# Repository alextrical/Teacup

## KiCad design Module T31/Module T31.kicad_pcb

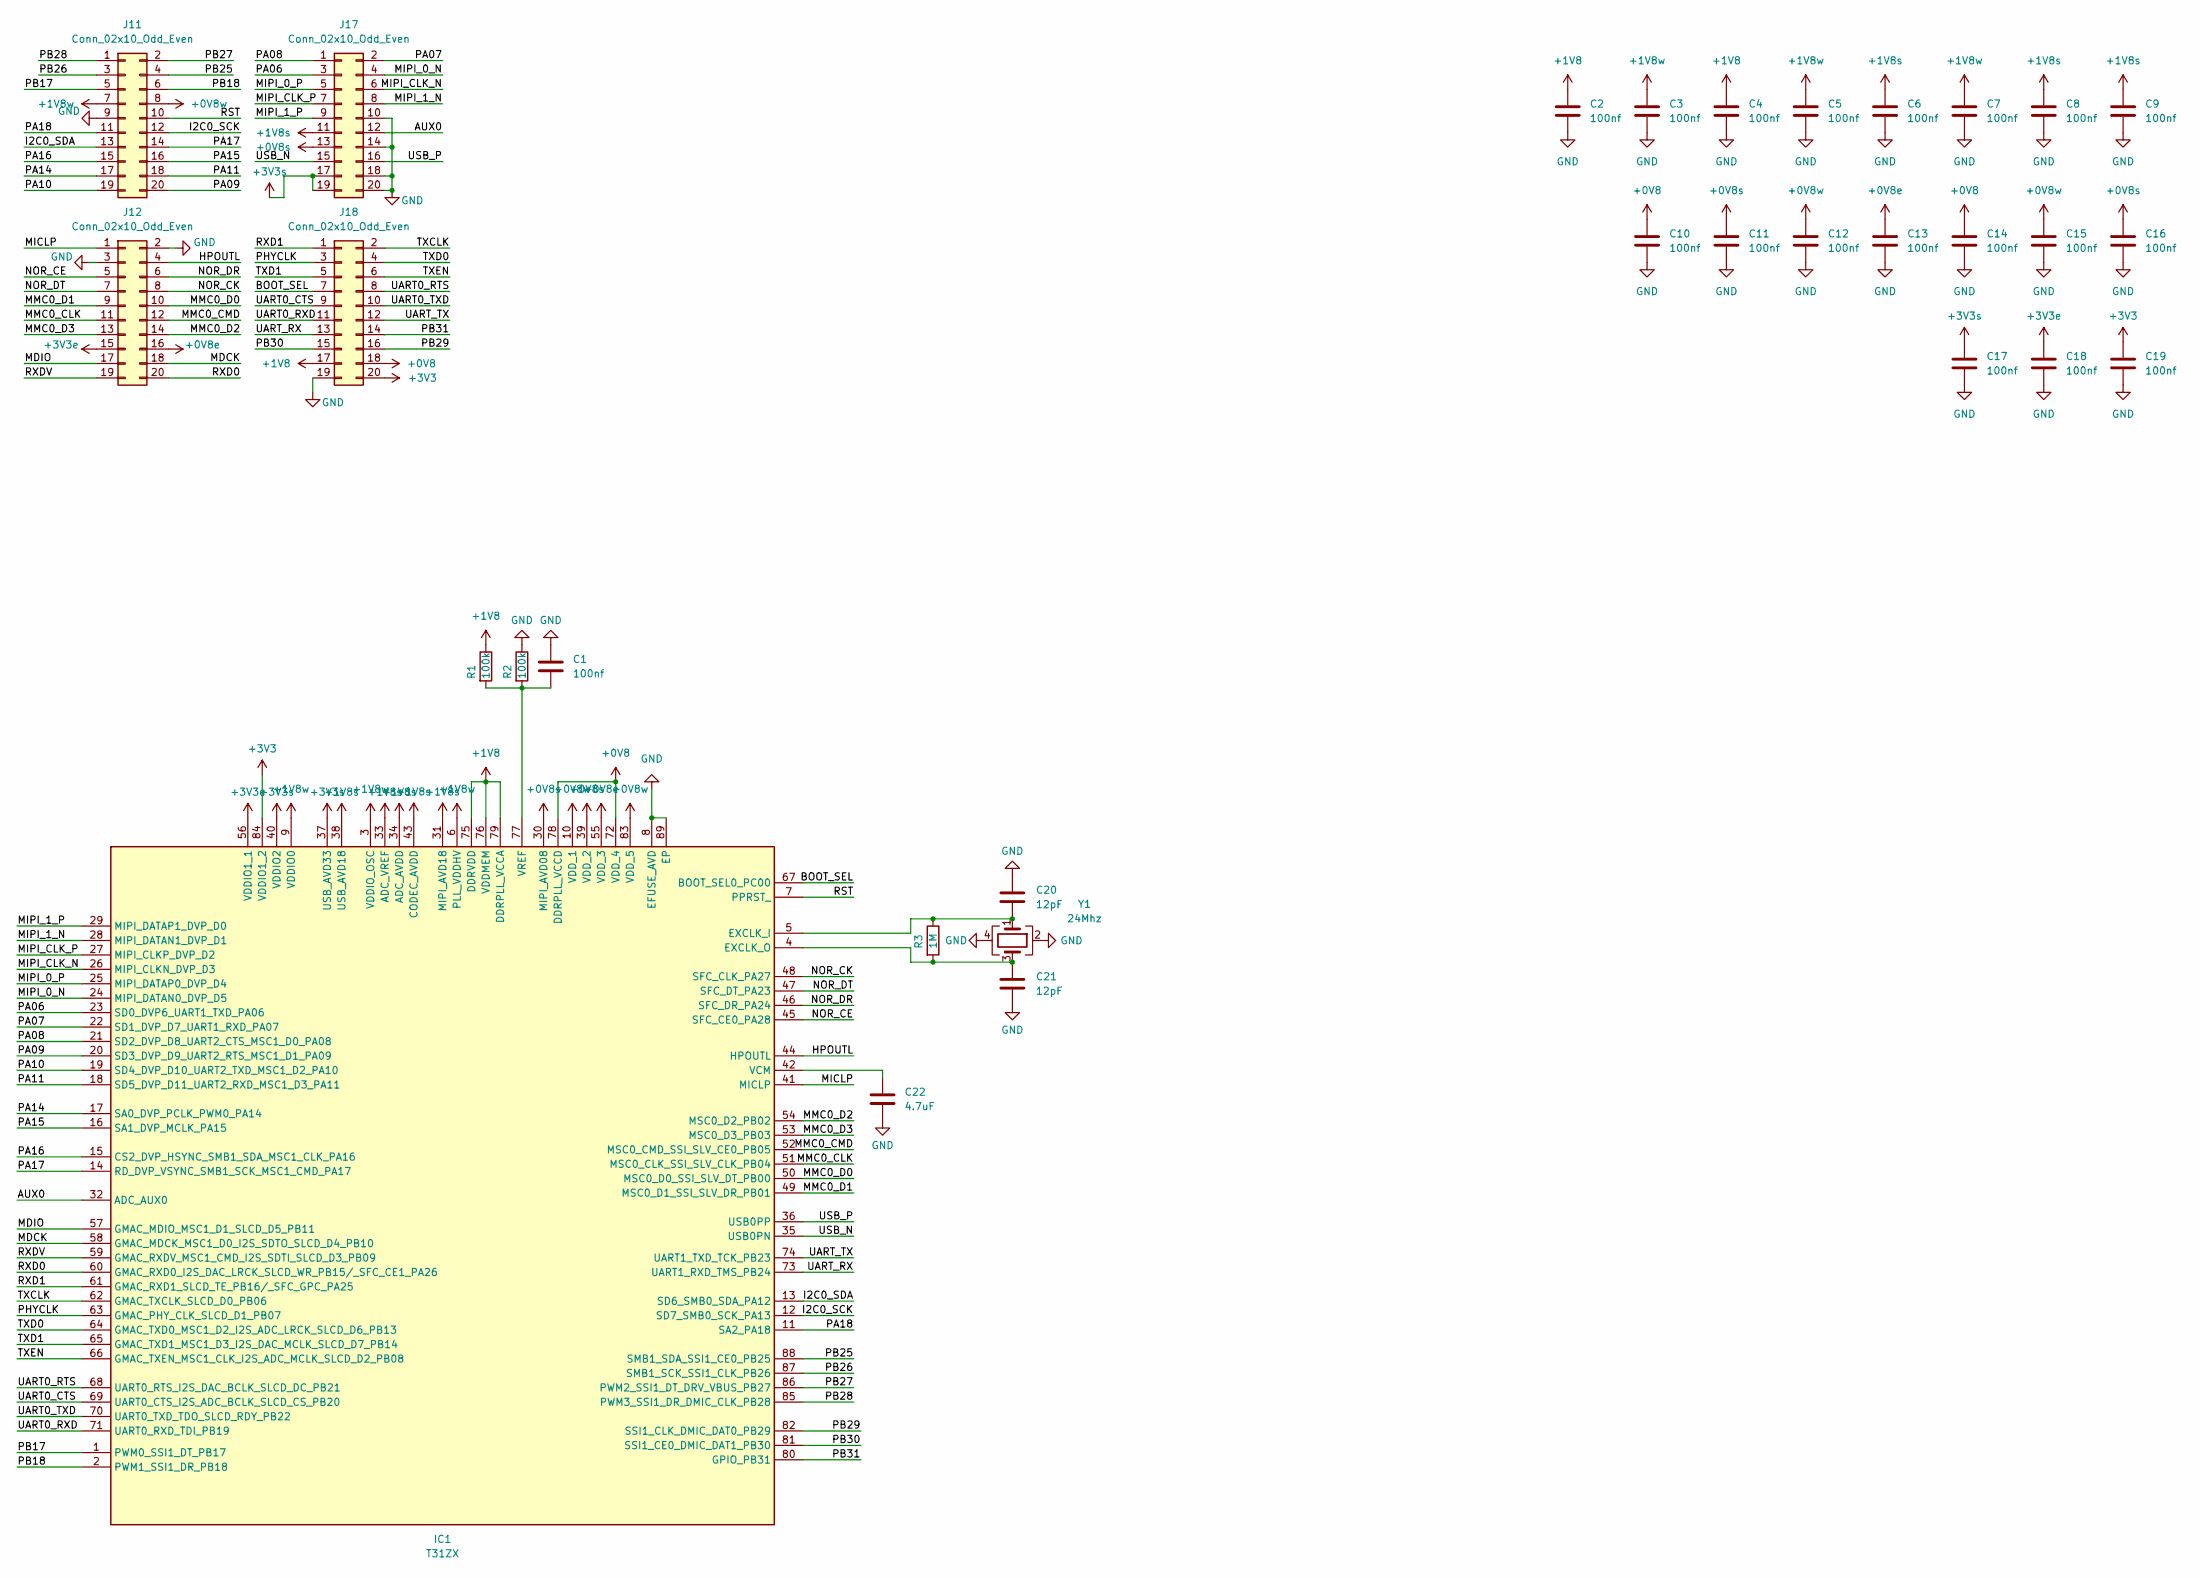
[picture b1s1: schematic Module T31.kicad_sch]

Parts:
C1, C2, C3, C4, C5, C6, C7, C8, C9, C10, C11, C12, C13, C14, C15, C16, C17, C18, C19: 100nf; C_0402_1005Metric; LCSC C1525
C20, C21: 12pF; C_0402_1005Metric; LCSC C1547
C22: 4.7uF; C_0402_1005Metric; LCSC C23733
IC1: T31ZX; QFN35P900X900X90-89N-D; Mouser Part Number 870-T31ZX
J11, J12, J17, J18: Conn_02x10_Odd_Even; PinHeader_2x10_P2.54mm_Vertical
R1, R2: 100k; R_0402_1005Metric; LCSC C25741
R3: 1M; R_0402_1005Metric; LCSC C26083
Y1: 24Mhz; Crystal_SMD_2016-4Pin_2.0x1.6mm; LCSC C557195

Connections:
+0V8: C10.1, C14.1, IC1.72 (VDD_4), IC1.78 (DDRPLL_VCCD), J18.18
+0V8e: C13.1, IC1.55 (VDD_3), J12.16
+0V8s: C11.1, C16.1, IC1.30 (MIPI_AVD08), IC1.39 (VDD_2), J17.13
+0V8w: C12.1, C15.1, IC1.10 (VDD_1), IC1.83 (VDD_5), J11.8
+1V8: C2.1, C4.1, IC1.75 (DDRVDD), IC1.76 (VDDMEM), IC1.79 (DDRPLL_VCCA), J18.17, R1.1
+1V8s: C6.1, C8.1, C9.1, IC1.31 (MIPI_AVD18), IC1.33 (ADC_VREF), IC1.34 (ADC_AVDD), IC1.38 (USB_AVD18), IC1.43 (CODEC_AVDD), J17.11
+1V8w: C3.1, C5.1, C7.1, IC1.3 (VDDIO_OSC), IC1.6 (PLL_VDDHV), IC1.9 (VDDIO0), J11.7
+3V3: C19.1, IC1.84 (VDDIO1_2), J18.20
+3V3e: C18.1, IC1.56 (VDDIO1_1), J12.15
+3V3s: C17.1, IC1.37 (USB_AVD33), IC1.40 (VDDIO2), J17.17, J17.19
/AUX0: IC1.32 (ADC_AUX0), J17.12
/BOOT_SEL: IC1.67 (BOOT_SEL0_PC00), J18.7
/HPOUTL: IC1.44 (HPOUTL), J12.4
/I2C0_SCK: IC1.12 (SD7_SMB0_SCK_PA13), J11.12
/I2C0_SDA: IC1.13 (SD6_SMB0_SDA_PA12), J11.13
/MDCK: IC1.58 (GMAC_MDCK_MSC1_D0_I2S_SDTO_SLCD_D4_PB10), J12.18
/MDIO: IC1.57 (GMAC_MDIO_MSC1_D1_SLCD_D5_PB11), J12.17
/MICLP: IC1.41 (MICLP), J12.1
/MIPI_0_N: IC1.24 (MIPI_DATAN0_DVP_D5), J17.4
/MIPI_0_P: IC1.25 (MIPI_DATAP0_DVP_D4), J17.5
/MIPI_1_N: IC1.28 (MIPI_DATAN1_DVP_D1), J17.8
/MIPI_1_P: IC1.29 (MIPI_DATAP1_DVP_D0), J17.9
/MIPI_CLK_N: IC1.26 (MIPI_CLKN_DVP_D3), J17.6
/MIPI_CLK_P: IC1.27 (MIPI_CLKP_DVP_D2), J17.7
/MMC0_CLK: IC1.51 (MSC0_CLK_SSI_SLV_CLK_PB04), J12.11
/MMC0_CMD: IC1.52 (MSC0_CMD_SSI_SLV_CE0_PB05), J12.12
/MMC0_D0: IC1.50 (MSC0_D0_SSI_SLV_DT_PB00), J12.10
/MMC0_D1: IC1.49 (MSC0_D1_SSI_SLV_DR_PB01), J12.9
/MMC0_D2: IC1.54 (MSC0_D2_PB02), J12.14
/MMC0_D3: IC1.53 (MSC0_D3_PB03), J12.13
/NOR_CE: IC1.45 (SFC_CE0_PA28), J12.5
/NOR_CK: IC1.48 (SFC_CLK_PA27), J12.8
/NOR_DR: IC1.46 (SFC_DR_PA24), J12.6
/NOR_DT: IC1.47 (SFC_DT_PA23), J12.7
/PA06: IC1.23 (SD0_DVP6_UART1_TXD_PA06), J17.3
/PA07: IC1.22 (SD1_DVP_D7_UART1_RXD_PA07), J17.2
/PA08: IC1.21 (SD2_DVP_D8_UART2_CTS_MSC1_D0_PA08), J17.1
/PA09: IC1.20 (SD3_DVP_D9_UART2_RTS_MSC1_D1_PA09), J11.20
/PA10: IC1.19 (SD4_DVP_D10_UART2_TXD_MSC1_D2_PA10), J11.19
/PA11: IC1.18 (SD5_DVP_D11_UART2_RXD_MSC1_D3_PA11), J11.18
/PA14: IC1.17 (SA0_DVP_PCLK_PWM0_PA14), J11.17
/PA15: IC1.16 (SA1_DVP_MCLK_PA15), J11.16
/PA16: IC1.15 (CS2_DVP_HSYNC_SMB1_SDA_MSC1_CLK_PA16), J11.15
/PA17: IC1.14 (RD_DVP_VSYNC_SMB1_SCK_MSC1_CMD_PA17), J11.14
/PA18: IC1.11 (SA2_PA18), J11.11
/PB17: IC1.1 (PWM0_SSI1_DT_PB17), J11.5
/PB18: IC1.2 (PWM1_SSI1_DR_PB18), J11.6
/PB25: IC1.88 (SMB1_SDA_SSI1_CE0_PB25), J11.4
/PB26: IC1.87 (SMB1_SCK_SSI1_CLK_PB26), J11.3
/PB27: IC1.86 (PWM2_SSI1_DT_DRV_VBUS_PB27), J11.2
/PB28: IC1.85 (PWM3_SSI1_DR_DMIC_CLK_PB28), J11.1
/PB29: IC1.82 (SSI1_CLK_DMIC_DAT0_PB29), J18.16
/PB30: IC1.81 (SSI1_CE0_DMIC_DAT1_PB30), J18.15
/PB31: IC1.80 (GPIO_PB31), J18.14
/PHYCLK: IC1.63 (GMAC_PHY_CLK_SLCD_D1_PB07), J18.3
/RST: IC1.7 (PPRST_), J11.10
/RXD0: IC1.60 (GMAC_RXD0_I2S_DAC_LRCK_SLCD_WR_PB15/_SF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), J12.20
/RXD1: IC1.61 (GMAC_RXD1_SLCD_TE_PB16/_SFC_GPC_PA25), J18.1
/RXDV: IC1.59 (GMAC_RXDV_MSC1_CMD_I2S_SDTI_SLCD_D3_PB09), J12.19
/TXCLK: IC1.62 (GMAC_TXCLK_SLCD_D0_PB06), J18.2
/TXD0: IC1.64 (GMAC_TXD0_MSC1_D2_I2S_ADC_LRCK_SLCD_D6_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), J18.4
/TXD1: IC1.65 (GMAC_TXD1_MSC1_D3_I2S_DAC_MCLK_SLCD_D7_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), J18.5
/TXEN: IC1.66 (GMAC_TXEN_MSC1_CLK_I2S_ADC_MCLK_SLCD_D2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), J18.6
/UART0_CTS: IC1.69 (UART0_CTS_I2S_ADC_BCLK_SLCD_CS_PB20), J18.9
/UART0_RTS: IC1.68 (UART0_RTS_I2S_DAC_BCLK_SLCD_DC_PB21), J18.8
/UART0_RXD: IC1.71 (UART0_RXD_TDI_PB19), J18.11
/UART0_TXD: IC1.70 (UART0_TXD_TDO_SLCD_RDY_PB22), J18.10
/UART_RX: IC1.73 (UART1_RXD_TMS_PB24), J18.13
/UART_TX: IC1.74 (UART1_TXD_TCK_PB23), J18.12
/USB_N: IC1.35 (USB0PN), J17.15
/USB_P: IC1.36 (USB0PP), J17.16
GND: C1.1, C2.2, C3.2, C4.2, C5.2, C6.2, C7.2, C8.2, C9.2, C10.2, C11.2, C12.2, C13.2, C14.2, C15.2, C16.2, C17.2, C18.2, C19.2, C20.1, C21.2, C22.2, IC1.8 (EFUSE_AVD), IC1.89 (EP), J11.9, J12.2, J12.3, J17.10, J17.14, J17.18, J17.20, J18.19, R2.1, Y1.2, Y1.4
unnamed: C20.2, IC1.5 (EXCLK_I), R3.1, Y1.1
unnamed: C21.1, IC1.4 (EXCLK_O), R3.2, Y1.3
unnamed: C22.1, IC1.42 (VCM)
unnamed: C1.2, IC1.77 (VREF), R1.2, R2.2

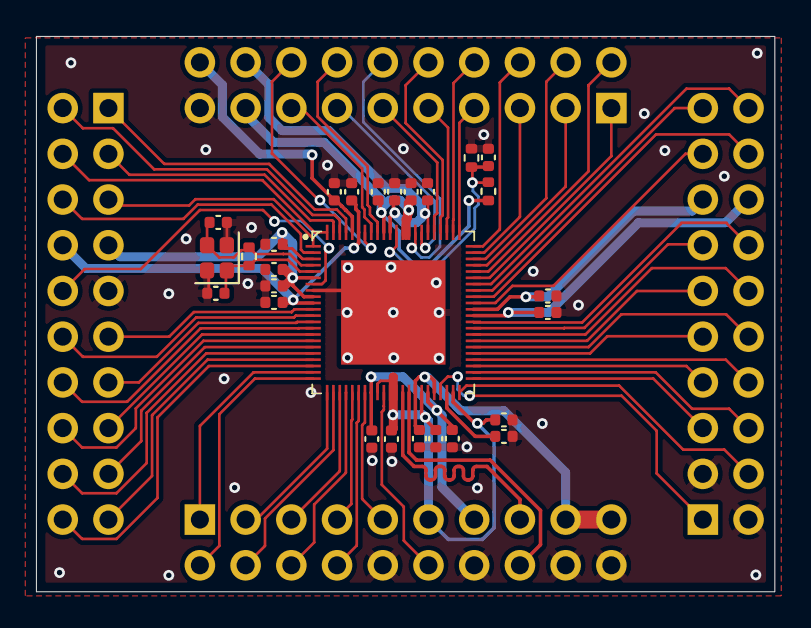
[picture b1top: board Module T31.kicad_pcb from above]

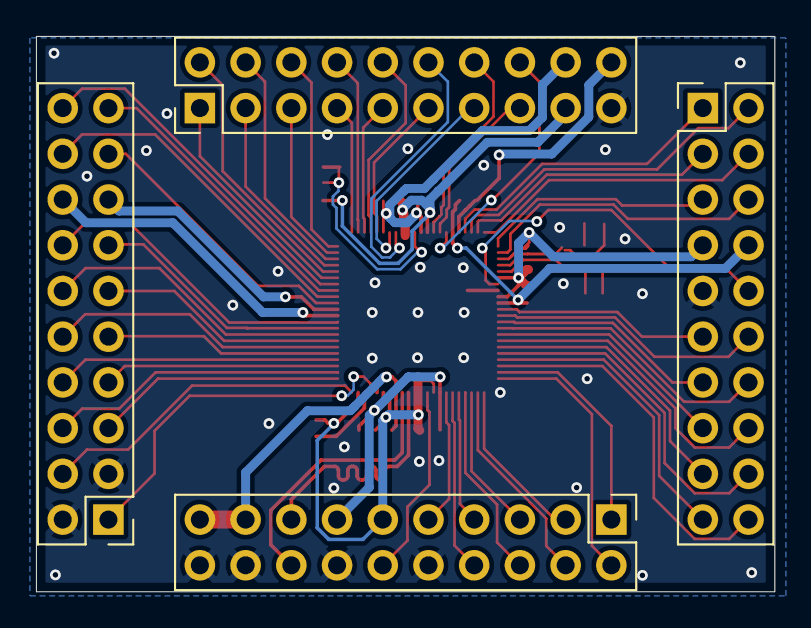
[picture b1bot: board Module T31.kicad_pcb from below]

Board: 4 copper layers, 41.0 x 30.8 mm, 31 parts (4 on the bottom side), 76 nets.

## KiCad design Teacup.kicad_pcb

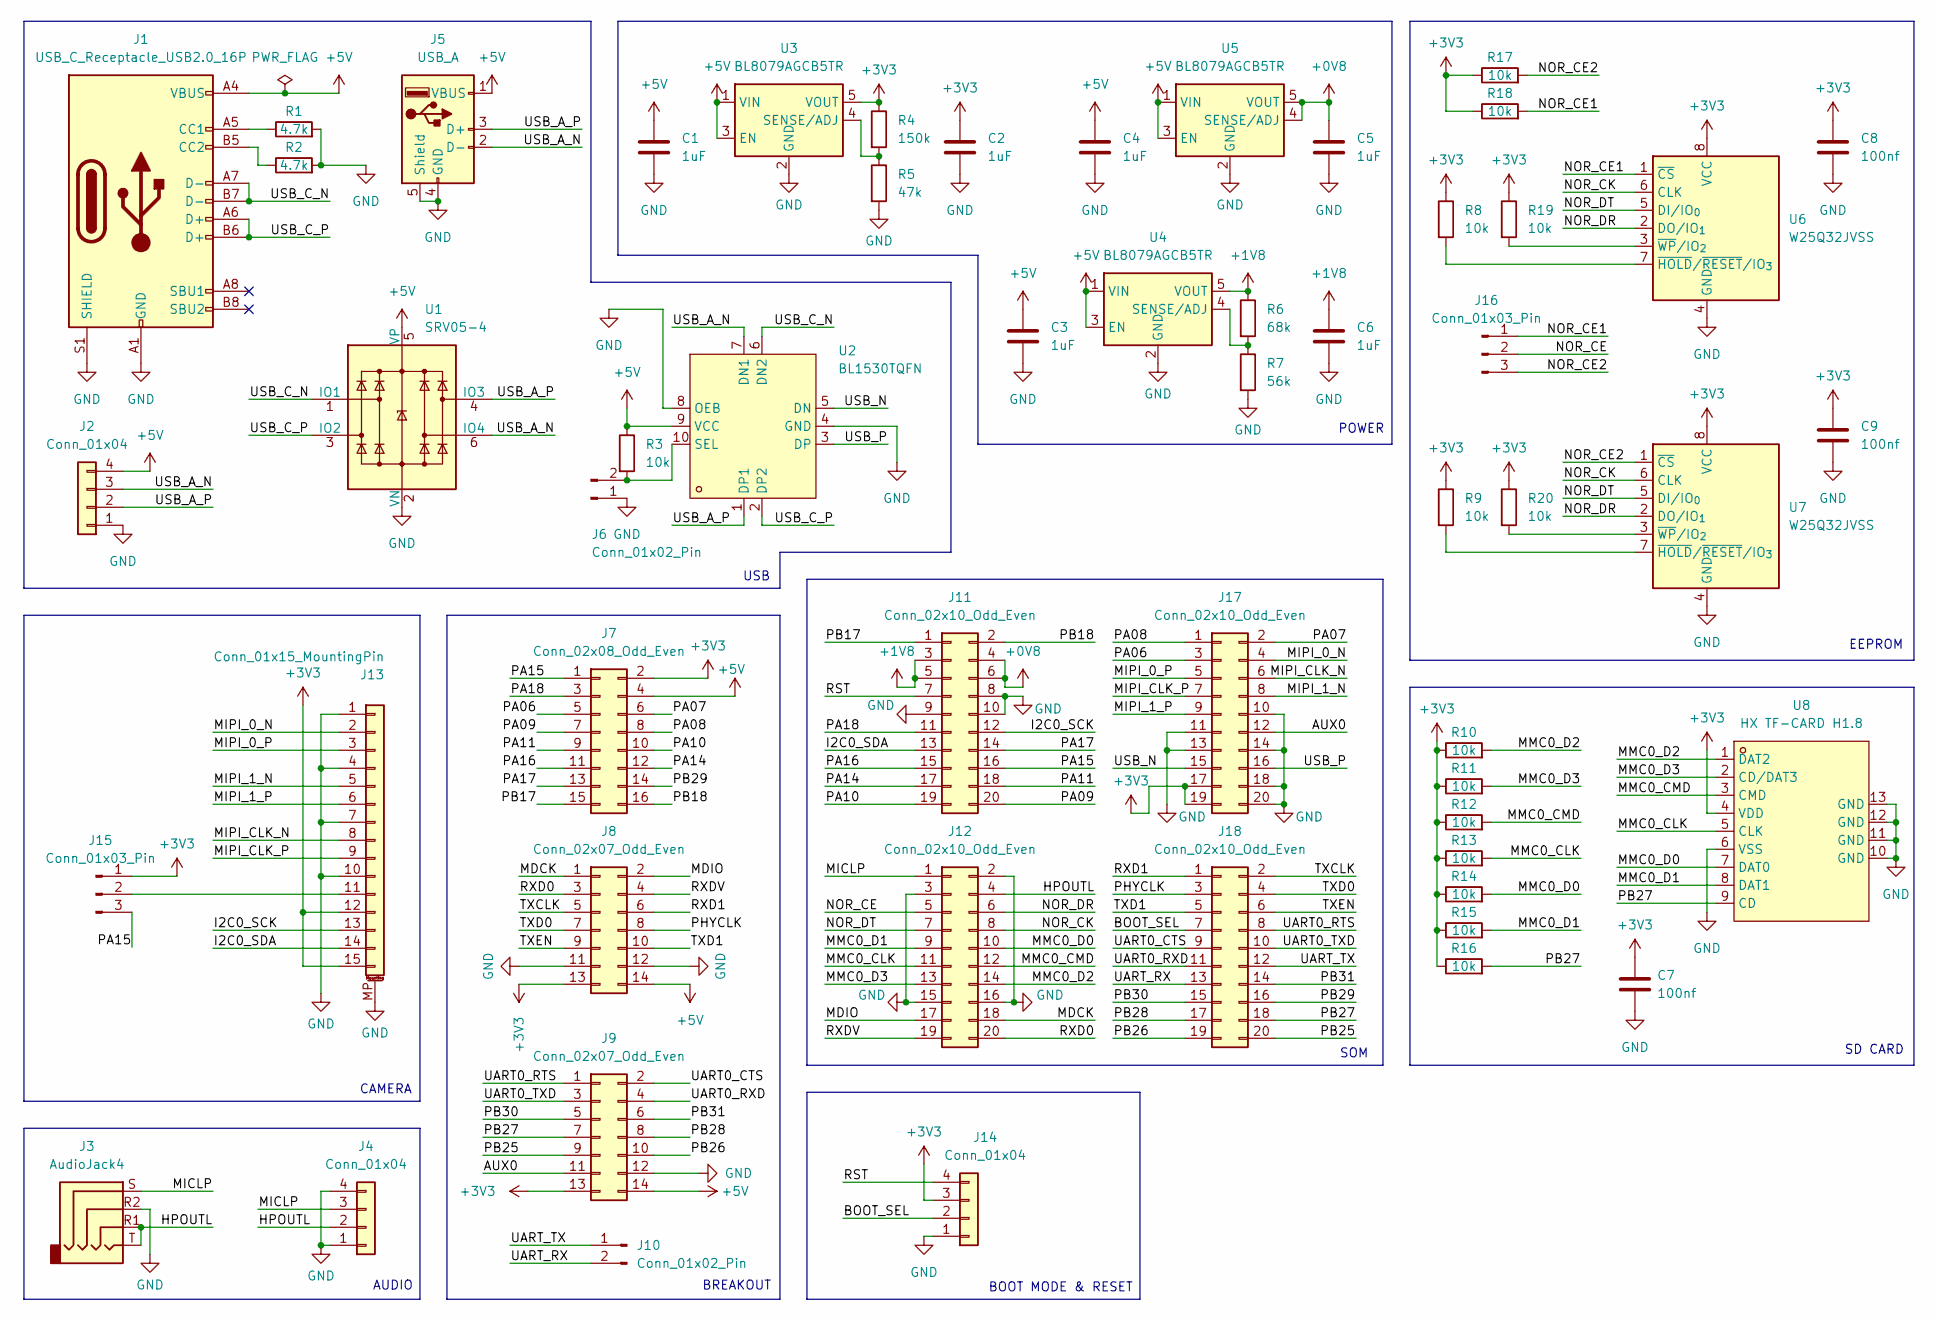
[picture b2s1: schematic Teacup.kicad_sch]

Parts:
C1, C2, C3, C4, C5, C6: 1uF; C_0402_1005Metric; LCSC C52923
C7, C8, C9: 100nf; C_0603_1608Metric; LCSC C14663
J1: USB_C_Receptacle_USB2.0_16P; USB_C_Receptacle_G-Switch_GT-USB-7010ASV; LCSC C36936538
J2, J4, J14: Conn_01x04; PinHeader_1x04_P2.54mm_Vertical
J3: AudioJack4; Jack_3.5mm_PJ320D_Horizontal
J5: USB_A; USB_A_Molex_67643_Horizontal
J6, J10: Conn_01x02_Pin; PinHeader_1x02_P2.54mm_Vertical
J7: Conn_02x08_Odd_Even; PinHeader_2x08_P2.54mm_Vertical
J8, J9: Conn_02x07_Odd_Even; PinHeader_2x07_P2.54mm_Vertical
J11, J12, J17, J18: Conn_02x10_Odd_Even; PinSocket_2x10_P2.54mm_Vertical
J13: Conn_01x15_MountingPin; JUSHUO_AFA07-S15FCA-00_1x15-1MP_P1.0mm_Horizontal
J15, J16: Conn_01x03_Pin; PinHeader_1x03_P2.54mm_Vertical
R1, R2: 4.7k; R_0402_1005Metric; LCSC C25900
R3, R8, R9, R10, R11, R12, R13, R14, R15, R16, R17, R18, R19, R20: 10k; R_0402_1005Metric; LCSC C25744
R4: 150k; R_0603_1608Metric; LCSC C22807
R5: 47k; R_0402_1005Metric; LCSC C25792
R6: 68k; R_0603_1608Metric; LCSC C23231
R7: 56k; R_0603_1608Metric; LCSC C23206
U1: SRV05-4; SOT-23-6; LCSC C7420376
U2: BL1530TQFN; UTQFN-10L_L1.8-W1.4-P0.40-BL; LCSC Part C313543
U3, U4, U5: BL8079AGCB5TR; TSOT-23-5; LCSC C5291411
U6: W25Q32JVSS; DIP-8_W7.62mm_Socket
U7: W25Q32JVSS; SOIC-8_5.3x5.3mm_P1.27mm
U8: HX TF-CARD H1.8; TF-SMD_HX-TF-CARD-H1.8-SY; LCSC Part C19189036

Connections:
+0V8: C5.1, J11.4, J11.6, U5.4 (SENSE/ADJ), U5.5 (VOUT)
+1V8: C6.1, J11.3, J11.5, R6.1, U4.5 (VOUT)
+3V3: C2.1, C7.1, C8.1, C9.1, J7.2, J8.13, J9.13, J13.12, J13.15, J14.3, J15.1, J17.17, J17.19, R4.1, R8.1, R9.1, R10.1, R11.1, R12.1, R13.1, R14.1, R15.1, R16.1, R17.1, R18.1, R19.1, R20.1, U3.5 (VOUT), U6.8 (VCC), U7.8 (VCC), U8.4 (VDD)
+5V: C1.1, C3.1, C4.1, J1.A4 (VBUS), J1.A9 (VBUS), J1.B4 (VBUS), J1.B9 (VBUS), J2.4, J5.1 (VBUS), J7.4, J8.14, J9.14, R3.1, U1.5 (VP), U2.9 (VCC), U3.1 (VIN), U3.3 (EN), U4.1 (VIN), U4.3 (EN), U5.1 (VIN), U5.3 (EN)
/AUX0: J9.11, J17.12
/BOOT_SEL: J14.2, J18.7
/HPOUTL: J3.R1, J3.T, J4.2, J12.4
/I2C0_SCK: J11.12, J13.13
/I2C0_SDA: J11.13, J13.14
/MDCK: J8.1, J12.18
/MDIO: J8.2, J12.17
/MICLP: J3.S, J4.3, J12.1
/MIPI_0_N: J13.2, J17.4
/MIPI_0_P: J13.3, J17.5
/MIPI_1_N: J13.5, J17.8
/MIPI_1_P: J13.6, J17.9
/MIPI_CLK_N: J13.8, J17.6
/MIPI_CLK_P: J13.9, J17.7
/MMC0_CLK: J12.11, R13.2, U8.5 (CLK)
/MMC0_CMD: J12.12, R12.2, U8.3 (CMD)
/MMC0_D0: J12.10, R14.2, U8.7 (DAT0)
/MMC0_D1: J12.9, R15.2, U8.8 (DAT1)
/MMC0_D2: J12.14, R10.2, U8.1 (DAT2)
/MMC0_D3: J12.13, R11.2, U8.2 (CD/DAT3)
/NOR_CE: J12.5, J16.2
/NOR_CE1: J16.1, R18.2, U6.1 (~CS)
/NOR_CE2: J16.3, R17.2, U7.1 (~CS)
/NOR_CK: J12.8, U6.6 (CLK), U7.6 (CLK)
/NOR_DR: J12.6, U6.2 (DO/IO_{1}), U7.2 (DO/IO_{1})
/NOR_DT: J12.7, U6.5 (DI/IO_{0}), U7.5 (DI/IO_{0})
/PA06: J7.5, J17.3
/PA07: J7.6, J17.2
/PA08: J7.8, J17.1
/PA09: J7.7, J11.20
/PA10: J7.10, J11.19
/PA11: J7.9, J11.18
/PA14: J7.12, J11.17
/PA15: J7.1, J11.16, J15.3
/PA16: J7.11, J11.15
/PA17: J7.13, J11.14
/PA18: J7.3, J11.11
/PB17: J7.15, J11.1
/PB18: J7.16, J11.2
/PB25: J9.9, J18.20
/PB26: J9.10, J18.19
/PB27: J9.7, J18.18, R16.2, U8.9 (CD)
/PB28: J9.8, J18.17
/PB29: J7.14, J18.16
/PB30: J9.5, J18.15
/PB31: J9.6, J18.14
/PHYCLK: J8.8, J18.3
/RST: J11.7, J14.4
/RXD0: J8.3, J12.20
/RXD1: J8.6, J18.1
/RXDV: J8.4, J12.19
/TXCLK: J8.5, J18.2
/TXD0: J8.7, J18.4
/TXD1: J8.10, J18.5
/TXEN: J8.9, J18.6
/UART0_CTS: J9.2, J18.9
/UART0_RTS: J9.1, J18.8
/UART0_RXD: J9.4, J18.11
/UART0_TXD: J9.3, J18.10
/UART_RX: J10.2, J18.13
/UART_TX: J10.1, J18.12
/USB_A_N: J2.3, J5.2 (D-), U1.6 (IO4), U2.7 (DN1)
/USB_A_P: J2.2, J5.3 (D+), U1.4 (IO3), U2.1 (DP1)
/USB_C_N: J1.A7 (D-), J1.B7 (D-), U1.1 (IO1), U2.6 (DN2)
/USB_C_P: J1.A6 (D+), J1.B6 (D+), U1.3 (IO2), U2.2 (DP2)
/USB_N: J17.15, U2.5 (DN)
/USB_P: J17.16, U2.3 (DP)
GND: C1.2, C2.2, C3.2, C4.2, C5.2, C6.2, C7.2, C8.2, C9.2, J1.A1 (GND), J1.A12 (GND), J1.B1 (GND), J1.B12 (GND), J1.S1 (SHIELD), J2.1, J3.R2, J4.1, J4.4, J5.4 (GND), J5.5 (Shield), J6.1, J8.11, J8.12, J9.12, J11.8, J11.9, J11.10, J12.2, J12.3, J12.15, J12.16, J13.1, J13.4, J13.7, J13.10, J13.MP (MountPin), J14.1, J17.10, J17.11, J17.13, J17.14, J17.18, J17.20, R1.2, R2.2, R5.2, R7.2, U1.2 (VN), U2.4 (GND), U2.8 (OEB), U3.2 (GND), U4.2 (GND), U5.2 (GND), U6.4 (GND), U7.4 (GND), U8.6 (VSS), U8.10 (GND), U8.11 (GND), U8.12 (GND), U8.13 (GND)
unnamed: J1.A5 (CC1), R1.1
unnamed: J1.B5 (CC2), R2.1
unnamed: J6.2, R3.2, U2.10 (SEL)
unnamed: J13.11, J15.2
unnamed: R4.2, R5.1, U3.4 (SENSE/ADJ)
unnamed: R6.2, R7.1, U4.4 (SENSE/ADJ)
unnamed: R8.2, U6.7 (~HOLD/~RESET/IO_{3})
unnamed: R19.2, U6.3 (~WP/IO_{2})
unnamed: R9.2, U7.7 (~HOLD/~RESET/IO_{3})
unnamed: R20.2, U7.3 (~WP/IO_{2})

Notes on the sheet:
SOM
BOOT MODE & RESET
EEPROM
POWER
SD CARD
CAMERA
BREAKOUT
AUDIO
USB

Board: 2 copper layers, 55 parts (0 on the bottom side), 82 nets, no tracks yet.

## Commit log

2026-03-25 Initial commit of modular system
2026-03-25 Update gitcheckout to v5 and remove panelize step from workflow
